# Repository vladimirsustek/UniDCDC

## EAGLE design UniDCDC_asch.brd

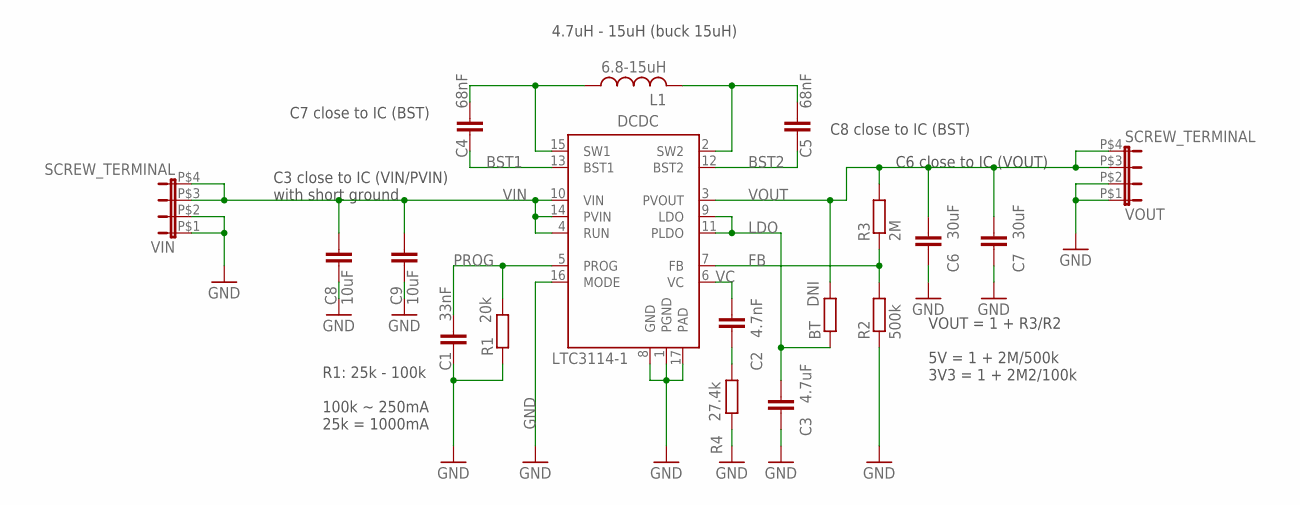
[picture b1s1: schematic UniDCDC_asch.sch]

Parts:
BT: DNI; R0805
C1: 33nF; C0805K
C2: 4.7nF; C0805K
C3: 4.7uF; C0805K
C4, C5: 68nF; C0805K
C6, C7: 30uF; C0805K
C8, C9: 10uF; C0805K
DCDC: LTC3114-1; TSSOP16
L1: 6.8-15uH; MSS1278_SMD
R1: 20k; R0805
R2: 500k; R0805
R3: 2M; R0805
R4: 27.4k; R0805
VIN: SCREW_TERMINAL
VOUT: SCREW_TERMINAL

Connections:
BST1: C4.2, DCDC.13 (BST1)
BST2: C5.2, DCDC.12 (BST2)
FB: DCDC.7 (FB), R2.2, R3.1
GND: C1.2, C3.2, C6.2, C7.2, C8.2, C9.2, DCDC.1 (PGND), DCDC.8 (GND), DCDC.16 (MODE), DCDC.17 (PAD), R1.1, R2.1, R4.1, VIN.P$1 (1), VIN.P$2 (2), VOUT.P$1 (1), VOUT.P$2 (2)
LDO: BT.1, C3.1, DCDC.9 (LDO), DCDC.11 (PLDO)
unnamed: C2.2, R4.2
unnamed: C4.1, DCDC.15 (SW1), L1.P$1 (1)
unnamed: C5.1, DCDC.2 (SW2), L1.P$2 (2)
PROG: C1.1, DCDC.5 (PROG), R1.2
VC: C2.1, DCDC.6 (VC)
VIN: C8.1, C9.1, DCDC.4 (RUN), DCDC.10 (VIN), DCDC.14 (PVIN), VIN.P$3 (3), VIN.P$4 (4)
VOUT: BT.2, C6.1, C7.1, DCDC.3 (PVOUT), R3.2, VOUT.P$3 (3), VOUT.P$4 (4)

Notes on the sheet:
C6 close to IC (VOUT)
C3 close to IC (VIN/PVIN) with short ground
C7 close to IC (BST)
C8 close to IC (BST)
R1: 25k - 100k 100k ~ 250mA 25k = 1000mA
4.7uH - 15uH (buck 15uH)
VOUT = 1 + R3/R2 5V = 1 + 2M/500k 3V3 = 1 + 2M2/100k

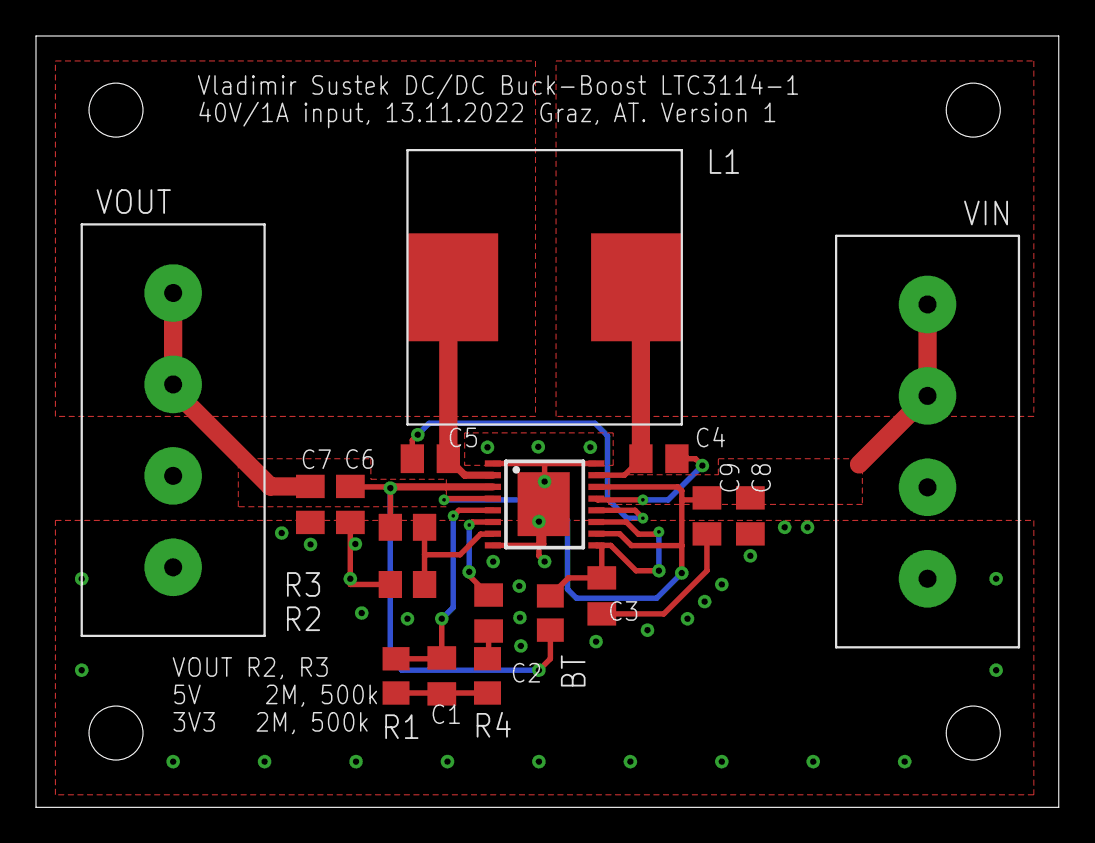
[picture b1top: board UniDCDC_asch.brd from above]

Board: 2 copper layers, 56.8 x 42.9 mm, 18 parts (0 on the bottom side), 12 nets.

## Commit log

2022-11-13 Manufacturing version
